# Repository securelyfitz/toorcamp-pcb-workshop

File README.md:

# toorcamp-pcb-workshop
Rapid prototyping is all the rage, but if that still involves too much foresight and planning for you, there's always reckless prototyping!

Never made a PCB before? This is the quickest way to learn. First, we'll give you a complete KiCAD schematic for a simple flashy light circuit. Next, we'll walk you through the process of laying out your first board. Finally, we'll show you how to fab it in minutes on a PCB milling machine! Made a mistake? No problem, fix it and you'll have V0.0.2 in your hands in a few more minutes.

# Disclaimer
This is a quick-and-dirty workshop. We're here to get your a little bit of experience in a short time. If you continue to make pcbs this way - it's well worth taking the time to focus on each of these steps in much more detail and understand *why* we do everyhing instead of just how.

# Customizing your board
1. [Install KiCad 6.0](https://www.kicad.org/download/)
2. Clone this repository, and open toorcamp-workshop.kicad_pro
3. From the KiCad project manager, open toorcamp-workshop.kicad_sch to look at the schematic. The schematic is already complete - What do you see?
4. From the KiCad project manager, open toorcamp-workshop.kicad_brd to look at the board layout. It is not complete - you need to customize it!
5. What shape do you want your board? You can adjust the outer border to change the shape. You can also make fancy shapes and curves with the line and curve too. Just make sure you have a closed shape - no leaks!
6. What layout do you want your LEDs? You can move them around for artistic intent.
7. Now - it's time to wire things up. Use the "Route Tracks (X)" tool to connect the light lines into actual copper lines. Make sure not to cross the streams!!!
8. Ready to mill the board? Choose File->Plot, and click 'PLOT' with all the default settings to generate the traces and edges. 
9. Click 'Generate Drill Files' to tell the mill where to make holes.

# Milling your board
1. Copy all your files to a USB stick, and go to the Milling PC
2. Open the Bantam Tools software if not already opened, and import your gerber file - it wants the f_cu file (front copper)
3. Make sure it also has your outline and drill file
4. Place the design on an empty spot on the blank board. 
5. Click 'mill' and cross your fingers!!

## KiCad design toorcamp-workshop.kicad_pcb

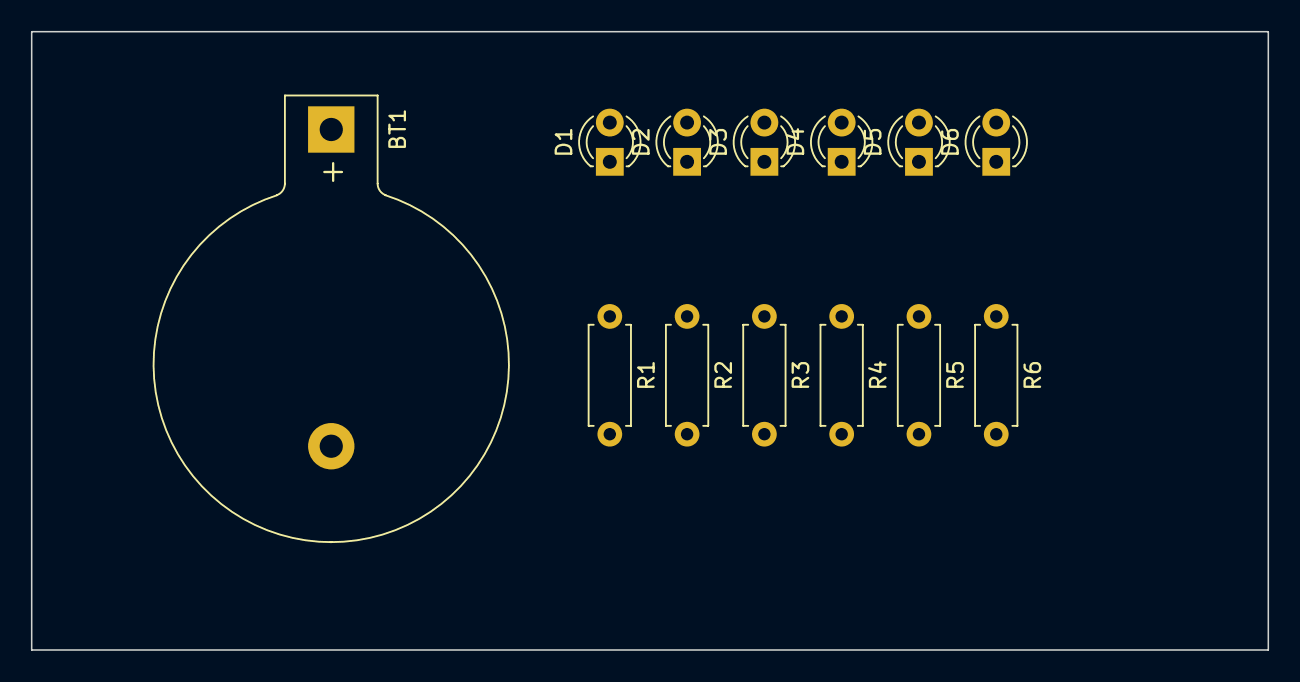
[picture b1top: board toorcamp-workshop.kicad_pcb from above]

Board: 2 copper layers, 80.0 x 40.0 mm, 13 parts (0 on the bottom side), 8 nets.

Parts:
BT1: Battery_Cell; BatteryHolder_Keystone_103_1x20mm
D1, D2, D3, D4, D5, D6: LED; LED_D3.0mm
R1, R2, R3, R4, R5, R6: R; R_Axial_DIN0207_L6.3mm_D2.5mm_P7.62mm_Horizontal

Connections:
unnamed: BT1.1 (+), D1.2 (A), D2.2 (A), D3.2 (A), D4.2 (A), D5.2 (A), D6.2 (A)
unnamed: BT1.2 (-), R1.2, R2.2, R3.2, R4.2, R5.2, R6.2
unnamed: D1.1 (K), R1.1
unnamed: D2.1 (K), R2.1
unnamed: D3.1 (K), R3.1
unnamed: D4.1 (K), R4.1
unnamed: D5.1 (K), R5.1
unnamed: D6.1 (K), R6.1

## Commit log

2022-07-14 set gerber output defaults
2022-07-14 adjust default dimensions
